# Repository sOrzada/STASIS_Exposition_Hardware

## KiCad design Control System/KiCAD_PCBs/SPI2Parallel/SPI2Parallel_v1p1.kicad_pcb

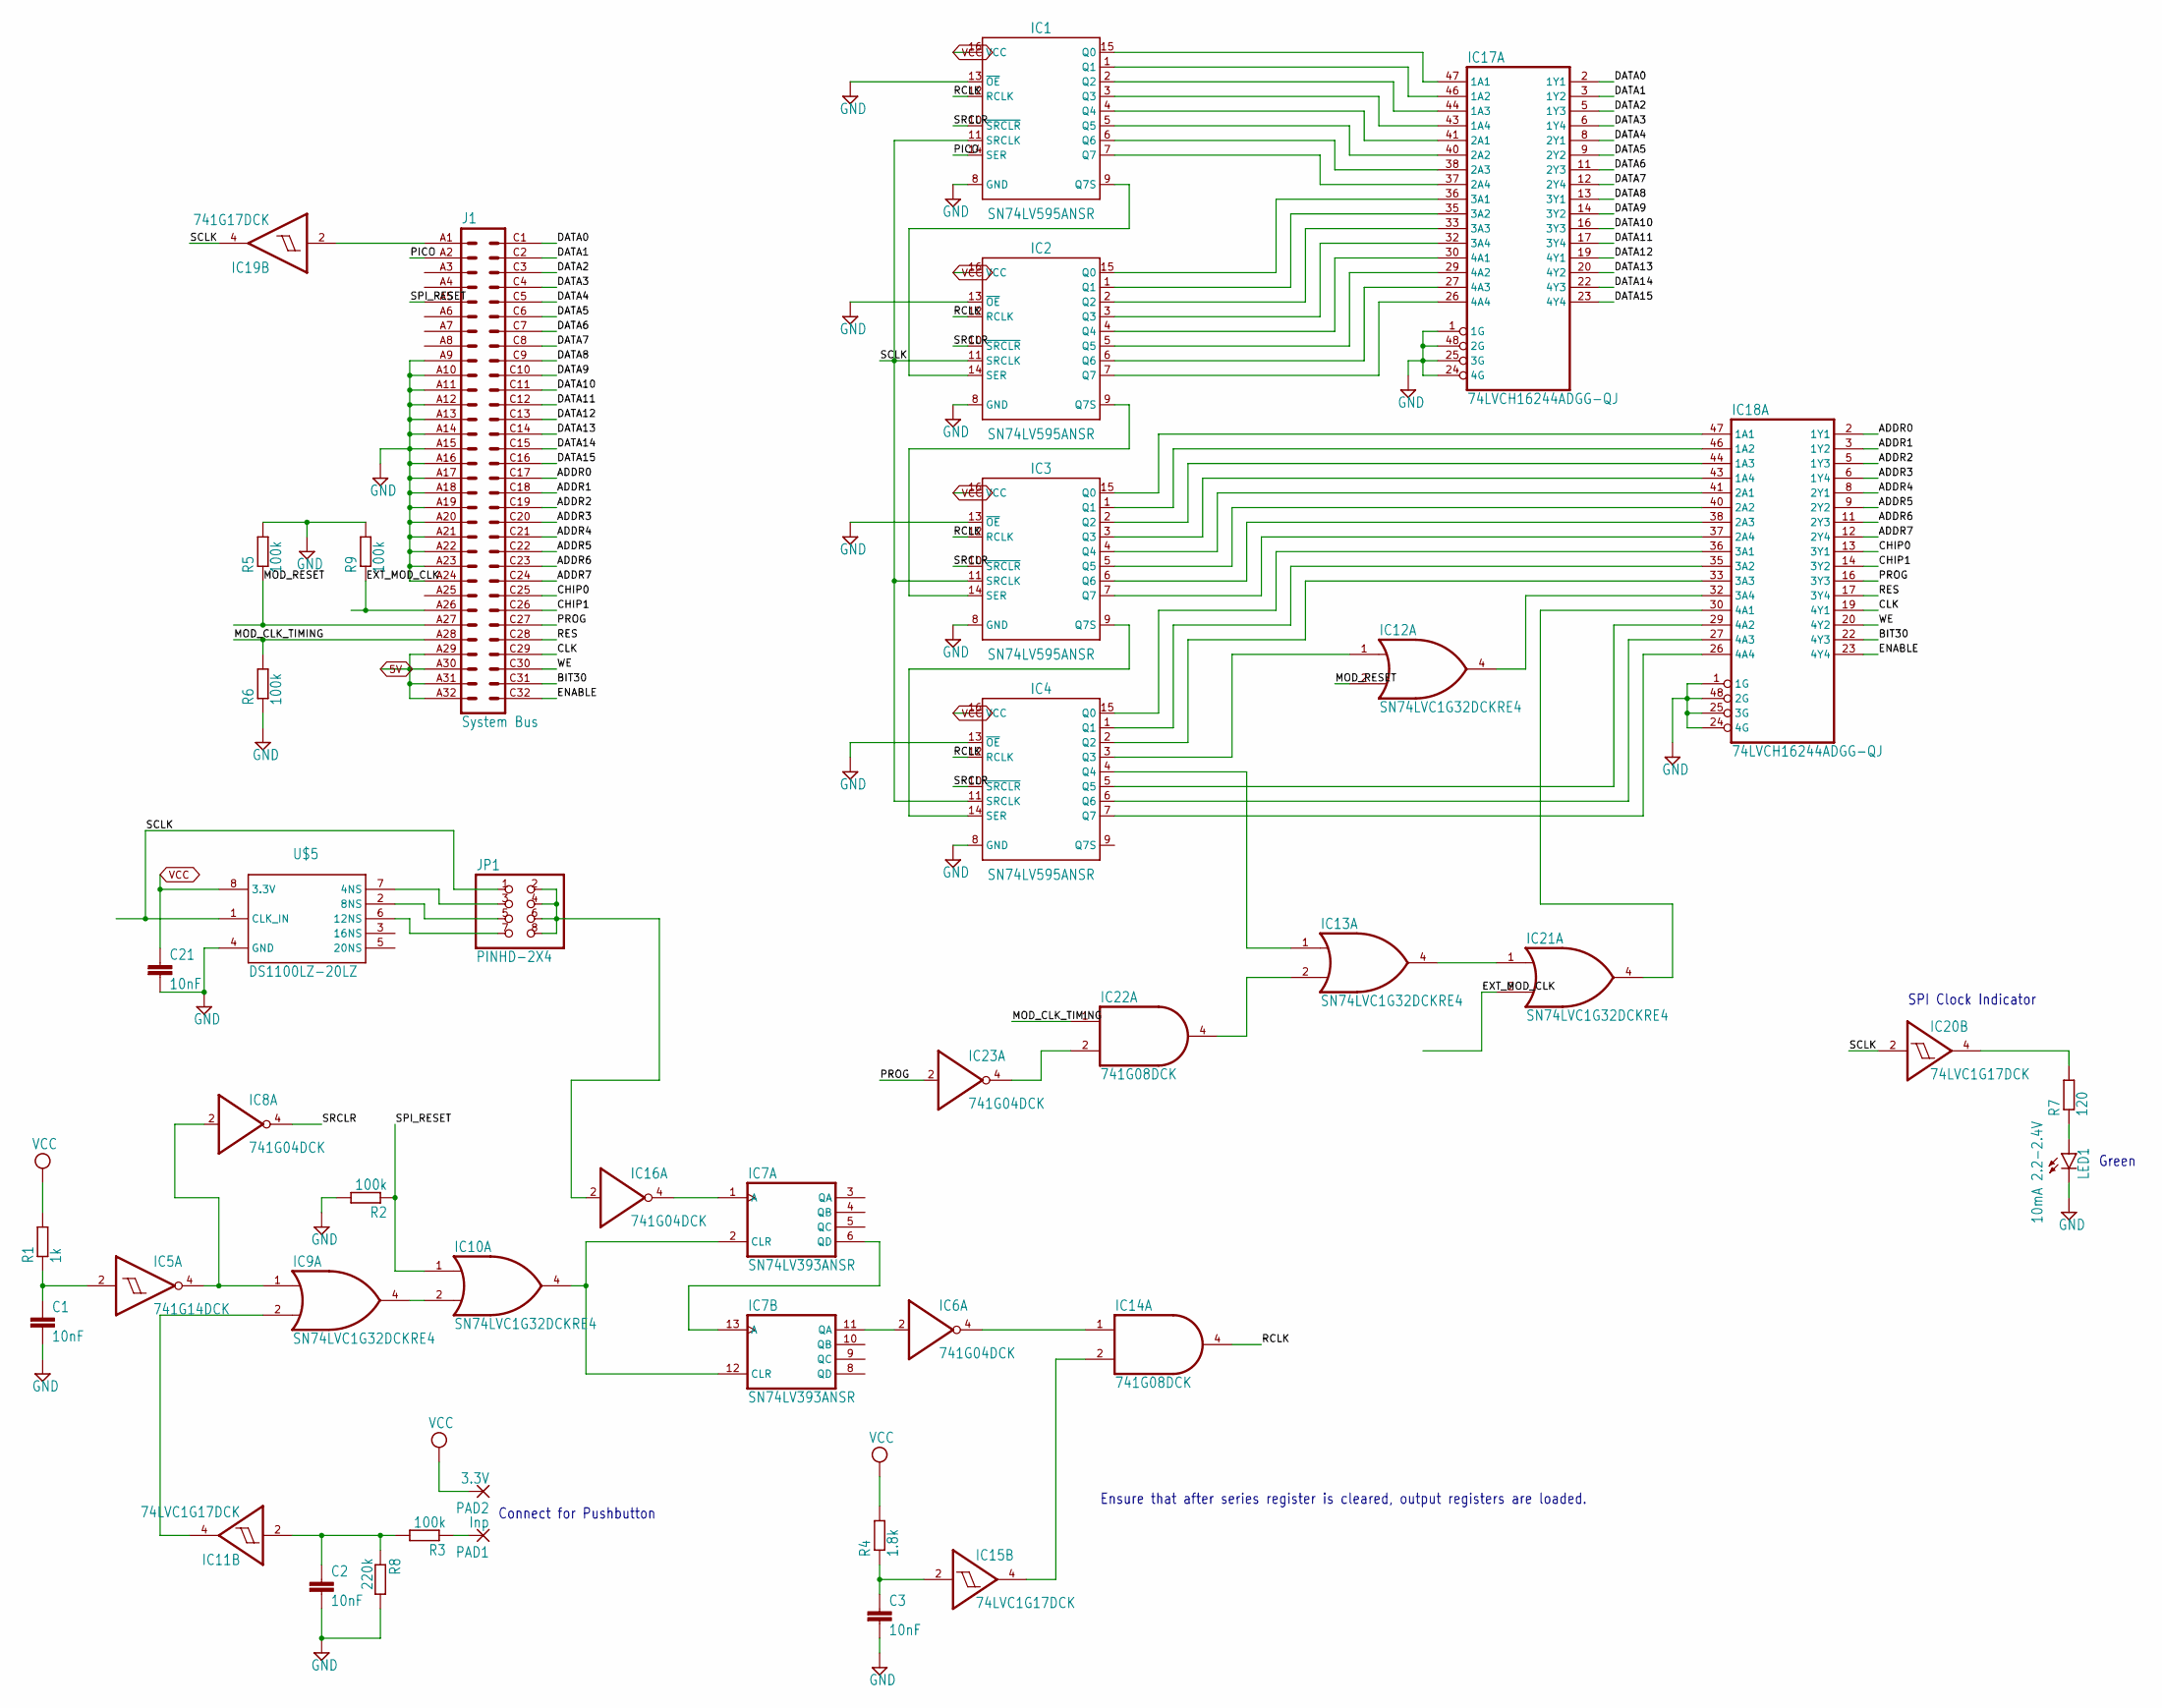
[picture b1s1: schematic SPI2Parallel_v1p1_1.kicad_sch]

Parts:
C1, C2, C3, C21: 10nF; C0603
IC1, IC2, IC3, IC4: SN74LV595ANSR; SOIC127P600X175-16N
IC5: 741G14DCK; SC70-5
IC6, IC8, IC16, IC23: 741G04DCK; SC70-5
IC7: SN74LV393ANSR; SO14
IC9, IC10, IC12, IC13, IC21: SN74LVC1G32DCKRE4; SC70-5
IC11, IC15, IC20: 74LVC1G17DCK; SC70-5
IC14, IC22: 741G08DCK; SC70-5
IC17, IC18: 74LVCH16244ADGG-QJ; SSOP48DL
IC19: 741G17DCK; SC70-5
J1: System Bus; VG64P
JP1: PINHD-2X4; 2X04
LED1: 10mA 2.2-2.4V; LED3MM
PAD1: Inp; SMD2,54-5,08
PAD2: 3.3V; SMD2,54-5,08
R1: 1k; R0603
R2, R3, R5, R6, R9: 100k; R0603
R4: 1.8k; R0603
R7: 120; R0603
R8: 220k; R0603
U$5: DS1100LZ-20LZ; SO-08

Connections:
5V: J1.A29, J1.A30, J1.A31, J1.A32; also elsewhere on the board
ADDR0: IC18.2 (1Y1), J1.C17
ADDR1: IC18.3 (1Y2), J1.C18
ADDR2: IC18.5 (1Y3), J1.C19
ADDR3: IC18.6 (1Y4), J1.C20
ADDR4: IC18.8 (2Y1), J1.C21
ADDR5: IC18.9 (2Y2), J1.C22
ADDR6: IC18.11 (2Y3), J1.C23
ADDR7: IC18.12 (2Y4), J1.C24
BIT30: IC18.22 (4Y3), J1.C31
CHIP0: IC18.13 (3Y1), J1.C25
CHIP1: IC18.14 (3Y2), J1.C26
CLK: IC18.19 (4Y1), J1.C29
DATA0: IC17.2 (1Y1), J1.C1
DATA1: IC17.3 (1Y2), J1.C2
DATA2: IC17.5 (1Y3), J1.C3
DATA3: IC17.6 (1Y4), J1.C4
DATA4: IC17.8 (2Y1), J1.C5
DATA5: IC17.9 (2Y2), J1.C6
DATA6: IC17.11 (2Y3), J1.C7
DATA7: IC17.12 (2Y4), J1.C8
DATA8: IC17.13 (3Y1), J1.C9
DATA9: IC17.14 (3Y2), J1.C10
DATA10: IC17.16 (3Y3), J1.C11
DATA11: IC17.17 (3Y4), J1.C12
DATA12: IC17.19 (4Y1), J1.C13
DATA13: IC17.20 (4Y2), J1.C14
DATA14: IC17.22 (4Y3), J1.C15
DATA15: IC17.23 (4Y4), J1.C16
ENABLE: IC18.23 (4Y4), J1.C32
EXT_MOD_CLK: IC21.2 (I1), J1.A26, R9.1
GND: C1.2, C2.2, C3.2, C21.2, IC1.8 (GND), IC1.13 (~OE), IC2.8 (GND), IC2.13 (~OE), IC3.8 (GND), IC3.13 (~OE), IC4.8 (GND), IC4.13 (~OE), IC5.3 (GND), IC6.3 (GND), IC7.7 (GND), IC8.3 (GND), IC9.3 (GND), IC10.3 (GND), IC11.3 (GND), IC12.3 (GND), IC13.3 (GND), IC14.3 (GND), IC15.3 (GND), IC16.3 (GND), IC17.1 (1G), IC17.4 (GND@1), IC17.10 (GND@2), IC17.15 (GND@3), IC17.21 (GND@4), IC17.24 (4G), IC17.25 (3G), IC17.28 (GND@5), IC17.34 (GND@6), IC17.39 (GND@7), IC17.45 (GND@8), IC17.48 (2G), IC18.1 (1G), IC18.4 (GND@1), IC18.10 (GND@2), IC18.15 (GND@3), IC18.21 (GND@4), IC18.24 (4G), IC18.25 (3G), IC18.28 (GND@5), IC18.34 (GND@6), IC18.39 (GND@7), IC18.45 (GND@8), IC18.48 (2G), IC19.3 (GND), IC20.3 (GND), IC21.3 (GND), IC22.3 (GND), IC23.3 (GND), J1.A9, J1.A10, J1.A11, J1.A12, J1.A13, J1.A14, J1.A15, J1.A16, J1.A17, J1.A18, J1.A19, J1.A20, J1.A21, J1.A22, J1.A23, J1.A24, LED1.K (C), R2.2, R5.2, R6.1, R8.2, R9.2, U$5.4 (GND); also elsewhere on the board
MOD_CLK_TIMING: IC22.1 (I0), J1.A28, R6.2
MOD_RESET: IC12.2 (I1), J1.A27, R5.1
unnamed: IC1.9 (Q7S), IC2.14 (SER)
unnamed: IC2.9 (Q7S), IC3.14 (SER)
unnamed: IC3.9 (Q7S), IC4.14 (SER)
unnamed: IC7.6 (QD), IC7.13 (A)
unnamed: IC6.2 (I), IC7.11 (QA)
unnamed: C1.1, IC5.2 (I), R1.1
unnamed: IC7.2 (CLR), IC7.12 (CLR), IC10.4 (O)
unnamed: IC9.4 (O), IC10.2 (I1)
unnamed: IC5.4 (O), IC8.2 (I), IC9.1 (I0)
unnamed: C2.1, IC11.2 (I), R3.2, R8.1
unnamed: IC9.2 (I1), IC11.4 (O)
unnamed: PAD1.1, R3.1
unnamed: IC4.3 (Q3), IC12.1 (I0)
unnamed: IC4.4 (Q4), IC13.1 (I0)
unnamed: IC6.4 (O), IC14.1 (I0)
unnamed: C3.1, IC15.2 (I), R4.1
unnamed: IC14.2 (I1), IC15.4 (O)
unnamed: IC7.1 (A), IC16.4 (O)
unnamed: IC1.15 (Q0), IC17.47 (1A1)
unnamed: IC1.1 (Q1), IC17.46 (1A2)
unnamed: IC1.2 (Q2), IC17.44 (1A3)
unnamed: IC1.3 (Q3), IC17.43 (1A4)
unnamed: IC1.4 (Q4), IC17.41 (2A1)
unnamed: IC1.5 (Q5), IC17.40 (2A2)
unnamed: IC1.6 (Q6), IC17.38 (2A3)
unnamed: IC1.7 (Q7), IC17.37 (2A4)
unnamed: IC2.15 (Q0), IC17.36 (3A1)
unnamed: IC2.1 (Q1), IC17.35 (3A2)
unnamed: IC2.2 (Q2), IC17.33 (3A3)
unnamed: IC2.3 (Q3), IC17.32 (3A4)
unnamed: IC2.4 (Q4), IC17.30 (4A1)
unnamed: IC2.5 (Q5), IC17.29 (4A2)
unnamed: IC2.6 (Q6), IC17.27 (4A3)
unnamed: IC2.7 (Q7), IC17.26 (4A4)
unnamed: IC3.15 (Q0), IC18.47 (1A1)
unnamed: IC3.1 (Q1), IC18.46 (1A2)
unnamed: IC3.2 (Q2), IC18.44 (1A3)
unnamed: IC3.3 (Q3), IC18.43 (1A4)
unnamed: IC3.4 (Q4), IC18.41 (2A1)
unnamed: IC3.5 (Q5), IC18.40 (2A2)
unnamed: IC3.6 (Q6), IC18.38 (2A3)
unnamed: IC3.7 (Q7), IC18.37 (2A4)
unnamed: IC4.15 (Q0), IC18.36 (3A1)
unnamed: IC4.1 (Q1), IC18.35 (3A2)
unnamed: IC4.2 (Q2), IC18.33 (3A3)
unnamed: IC12.4 (O), IC18.32 (3A4)
unnamed: IC18.30 (4A1), IC21.4 (O)
unnamed: IC4.5 (Q5), IC18.29 (4A2)
unnamed: IC4.6 (Q6), IC18.27 (4A3)
unnamed: IC4.7 (Q7), IC18.26 (4A4)
unnamed: IC16.2 (I), JP1.2, JP1.4, JP1.6, JP1.8
unnamed: JP1.7, U$5.6 (12NS)
unnamed: JP1.3, U$5.7 (4NS)
unnamed: JP1.5, U$5.2 (8NS)
unnamed: IC19.2 (I), J1.A1
unnamed: IC13.4 (O), IC21.1 (I0)
unnamed: IC13.2 (I1), IC22.4 (O)
unnamed: IC22.2 (I1), IC23.4 (O)
unnamed: IC20.4 (O), R7.2
unnamed: LED1.A, R7.1
PICO: IC1.14 (SER), J1.A2
PROG: IC18.16 (3Y3), IC23.2 (I), J1.C27
RCLK: IC1.12 (RCLK), IC2.12 (RCLK), IC3.12 (RCLK), IC4.12 (RCLK), IC14.4 (O)
RES: IC18.17 (3Y4), J1.C28
SCLK: IC1.11 (SRCLK), IC2.11 (SRCLK), IC3.11 (SRCLK), IC4.11 (SRCLK), IC19.4 (O), IC20.2 (I), JP1.1, U$5.1 (CLK_IN)
SPI_RESET: IC10.1 (I0), J1.A5, R2.1
SRCLR: IC1.10 (~SRCLR), IC2.10 (~SRCLR), IC3.10 (~SRCLR), IC4.10 (~SRCLR), IC8.4 (O)
VCC: C21.1, IC1.16 (VCC), IC2.16 (VCC), IC3.16 (VCC), IC4.16 (VCC), IC5.5 (VCC), IC6.5 (VCC), IC7.14 (VCC), IC8.5 (VCC), IC9.5 (VCC), IC10.5 (VCC), IC11.5 (VCC), IC12.5 (VCC), IC13.5 (VCC), IC14.5 (VCC), IC15.5 (VCC), IC16.5 (VCC), IC17.7 (VCC@1), IC17.18 (VCC@2), IC17.31 (VCC@3), IC17.42 (VCC@4), IC18.7 (VCC@1), IC18.18 (VCC@2), IC18.31 (VCC@3), IC18.42 (VCC@4), IC19.5 (VCC), IC20.5 (VCC), IC21.5 (VCC), IC22.5 (VCC), IC23.5 (VCC), PAD2.1, R1.2, R4.2, U$5.8 (3.3V); also elsewhere on the board
WE: IC18.20 (4Y2), J1.C30

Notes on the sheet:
Green
Connect for Pushbutton
SPI Clock Indicator
Ensure that after series register is cleared, output registers are loaded.

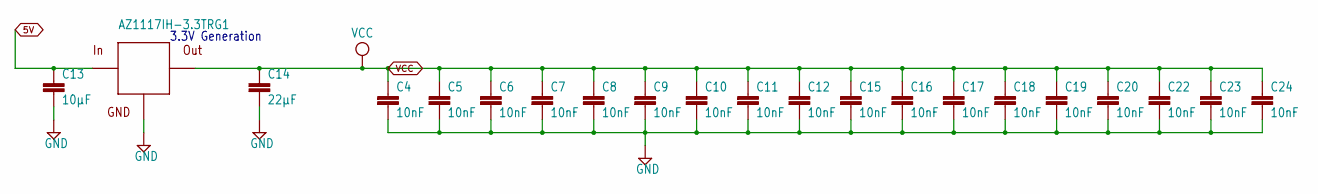
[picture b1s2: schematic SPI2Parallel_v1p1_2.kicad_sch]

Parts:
C4, C5, C6, C7, C8, C9, C10, C11, C12, C15, C16, C17, C18, C19, C20, C22, C23, C24: 10nF; C0603
C13: 10µF; C1206
C14: 22µF; C1206
U$9: AZ1117IH-3.3TRG1; SOT223

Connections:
5V: C13.1, U$9.3 (IN); also elsewhere on the board
GND: C4.2, C5.2, C6.2, C7.2, C8.2, C9.2, C10.2, C11.2, C12.2, C13.2, C14.2, C15.2, C16.2, C17.2, C18.2, C19.2, C20.2, C22.2, C23.2, C24.2, U$9.1 (GND); also elsewhere on the board
VCC: C4.1, C5.1, C6.1, C7.1, C8.1, C9.1, C10.1, C11.1, C12.1, C14.1, C15.1, C16.1, C17.1, C18.1, C19.1, C20.1, C22.1, C23.1, C24.1, U$9.2 (VCC), U$9.4 (VCC); also elsewhere on the board

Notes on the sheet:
3.3V Generation

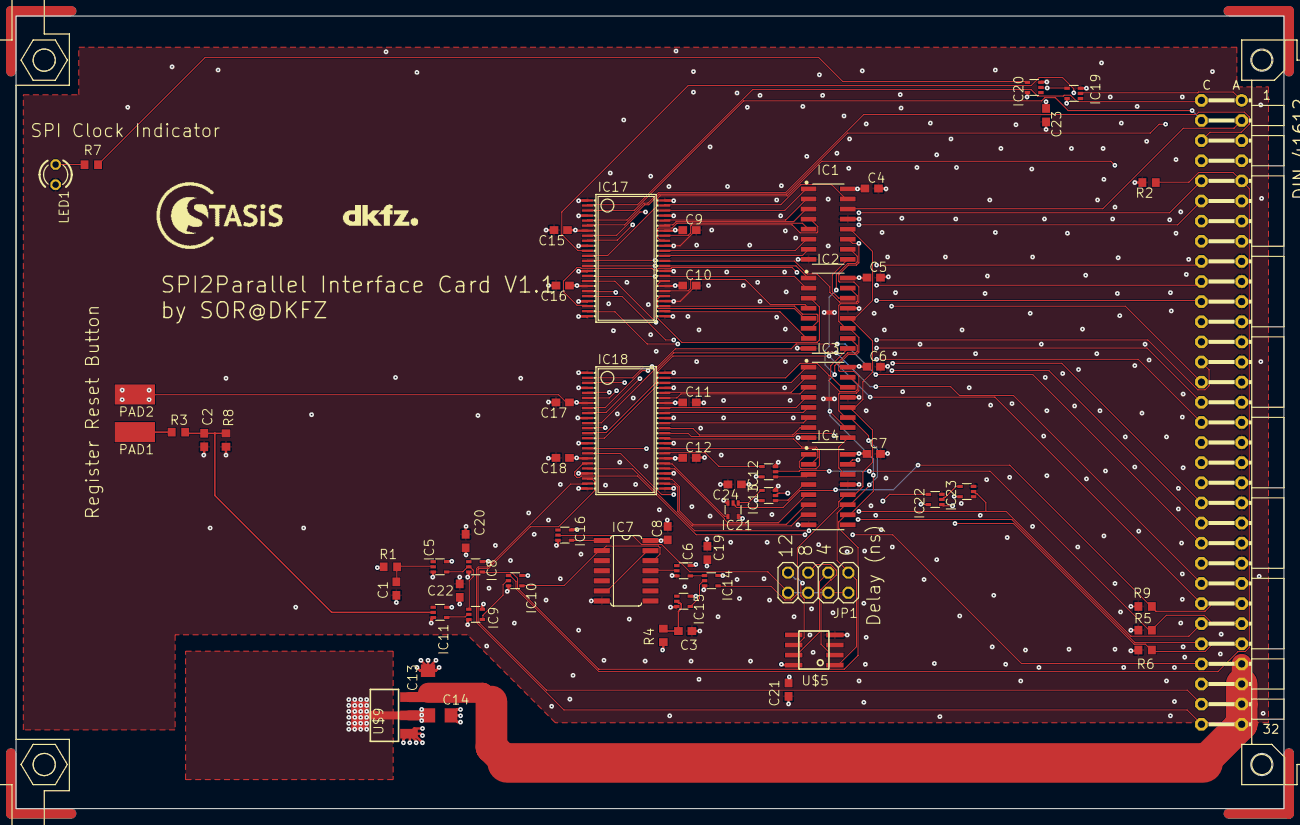
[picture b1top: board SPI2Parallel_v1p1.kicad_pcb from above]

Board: 4 copper layers, 160.0 x 100.0 mm, 65 parts (0 on the bottom side), 103 nets.

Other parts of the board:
U$1: LOGO_STASIS
U$2: LOGO_DKFZ
